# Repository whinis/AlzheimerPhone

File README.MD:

# Arduino Alzheimers Phone

A project for a friend. This modifies a Cordtelco 2500 model telephone so that it 
effectively only works as a speed dial however has a 911 override. Its designed with 
alzheimers in mind so that if the person continues to try and dial the phone only 
the first number matters fixing what is seen as a defect in current phones you can buy for alzheimers.

I have included the PCB in kicad I used to make this phone, Also the arduino code. The board uses a
at328p microprocessor with an 8mhz crystal as the voltage on a phone line can vary wildly and 5v cannot
be assured. It programs as if its an arduino pro mini

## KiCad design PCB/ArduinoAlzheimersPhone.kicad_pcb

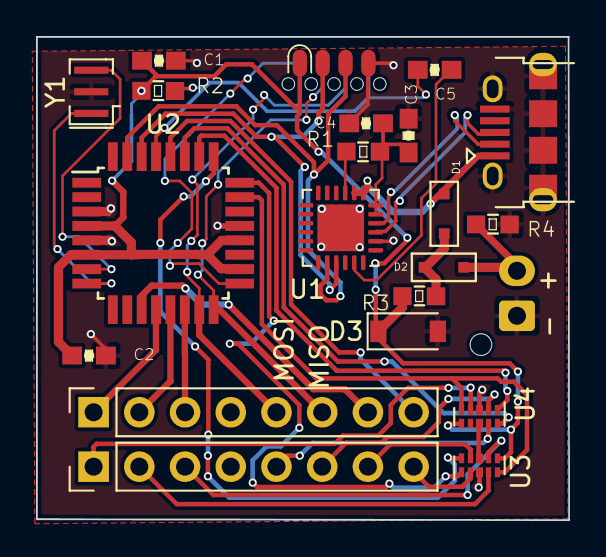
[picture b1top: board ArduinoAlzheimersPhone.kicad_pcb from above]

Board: 2 copper layers, 29.6 x 26.8 mm, 22 parts (0 on the bottom side), 36 nets.

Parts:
C1, C3: 1uf; C0603
C2, C4, C5: 100nf; C0603
D1, D2: 1N4148WX-TP; SOD-323
D3: 5.1V; D_SOD-123
J1: Conn_02x04_Odd_Even; SOIC_clipProgSmall
J2: USB_B_Micro; USB_Micro-B_Amphenol_10118194-0001LF_Horizontal
J3: Conn_01x08; PinHeader_1x08_P2.54mm_Vertical
J4: Conn_01x08; PinSocket_1x08_P2.54mm_Vertical
J5: Conn_01x02; JST_XH_B2B-XH-AM_1x02_P2.50mm_Vertical
R1, R2, R4: 10k; R0603
R3: 20; R0603
U1: CP2102N-A01-GQFN24; QFN-24-1EP_4x4mm_P0.5mm_EP2.6x2.6mm
U2: ATMEGA328P-MU; TQFP-32_7x7mm_P0.8mm
U3, U4: TMUX1204; USON-10_2.5x1.0mm_P0.5mm
Y1: 16mhz; Resonator_SMD_muRata_CSTxExxV-3Pin_3.0x1.1mm

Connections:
/3v3: C3.1, C4.1, R1.1, U1.5, U1.6
/5v: C1.1, C2.1, D3.1, J1.1, R2.1, R3.1, U2.4, U2.6, U2.18, U2.20, U3.6, U4.6
/5v_RAW: D1.C, D2.C, R3.2
/5v_USB: D1.A, J2.1, U1.7, U1.8
/10v: D2.A, J5.2, R4.1
/D+: J2.3, U1.3
/D-: J2.2, U1.4
/DTR: C5.2, U1.23
/KEYPAD_C1: J1.4, J4.6, U2.16
/KEYPAD_C2: J1.6, J4.5, U2.15
/KEYPAD_C3: J4.1, U2.12
/KEYPAD_COM: U3.8, U4.8
/KEYPAD_EN: U2.23, U3.5, U4.5
/KEYPAD_R1: J4.8, U2.28
/KEYPAD_R2: J4.7, U2.11
/KEYPAD_R3: J4.2, U2.13
/KEYPAD_R4: J4.3, U2.14
/PHONE_C1: J3.6, U4.2
/PHONE_C2: J3.5, U4.9
/PHONE_C3: J3.1, U4.4
/PHONE_C_A0: U2.26, U4.1
/PHONE_C_A1: U2.27, U4.10
/PHONE_R1: J3.8, U3.2
/PHONE_R2: J3.7, U3.9
/PHONE_R3: J3.2, U3.4
/PHONE_R4: J3.3, U3.7
/PHONE_R_A0: U2.24, U3.1
/PHONE_R_A1: U2.25, U3.10
/RST: C5.1, J1.8, R2.2, U2.29
/RX: J1.3, U1.21, U2.30
/SCK: J1.2, U2.17
/TX: J1.5, U1.20, U2.31
/USART_RST: R1.2, U1.9
GND: C1.2, C2.2, C3.2, C4.2, D3.2, J1.7, J2.5, J2.6, J5.1, R4.2, U1.2, U1.25, U2.3, U2.5, U2.21, U3.3, U4.3, Y1.2
unnamed: U2.7, Y1.3
unnamed: U2.8, Y1.1

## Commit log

2020-11-14 A project for a friend. This modifies a Cordtelco 2500 model telephone so that it effectively only works as a speed dial however has a 911 override. Its designed with alzheimers in mind so that if th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
